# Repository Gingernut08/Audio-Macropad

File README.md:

Full Design:

Schematic:

PCB:

Case:

The Case fits together with 4x M3 Bolts and heatset inserts

BOM
16x Cherry MX Switches
16x DSA Keycaps
4x M3x5x4 Heatset inserts
4x M3x16mm SHCS Bolts
16x 1N4148 DO-35 Diodes.
16x SK6812 MINI-E LEDs
1x 0.91" 128x32 OLED Display
1x XIAO RP2040
1x Case (2 printed parts)

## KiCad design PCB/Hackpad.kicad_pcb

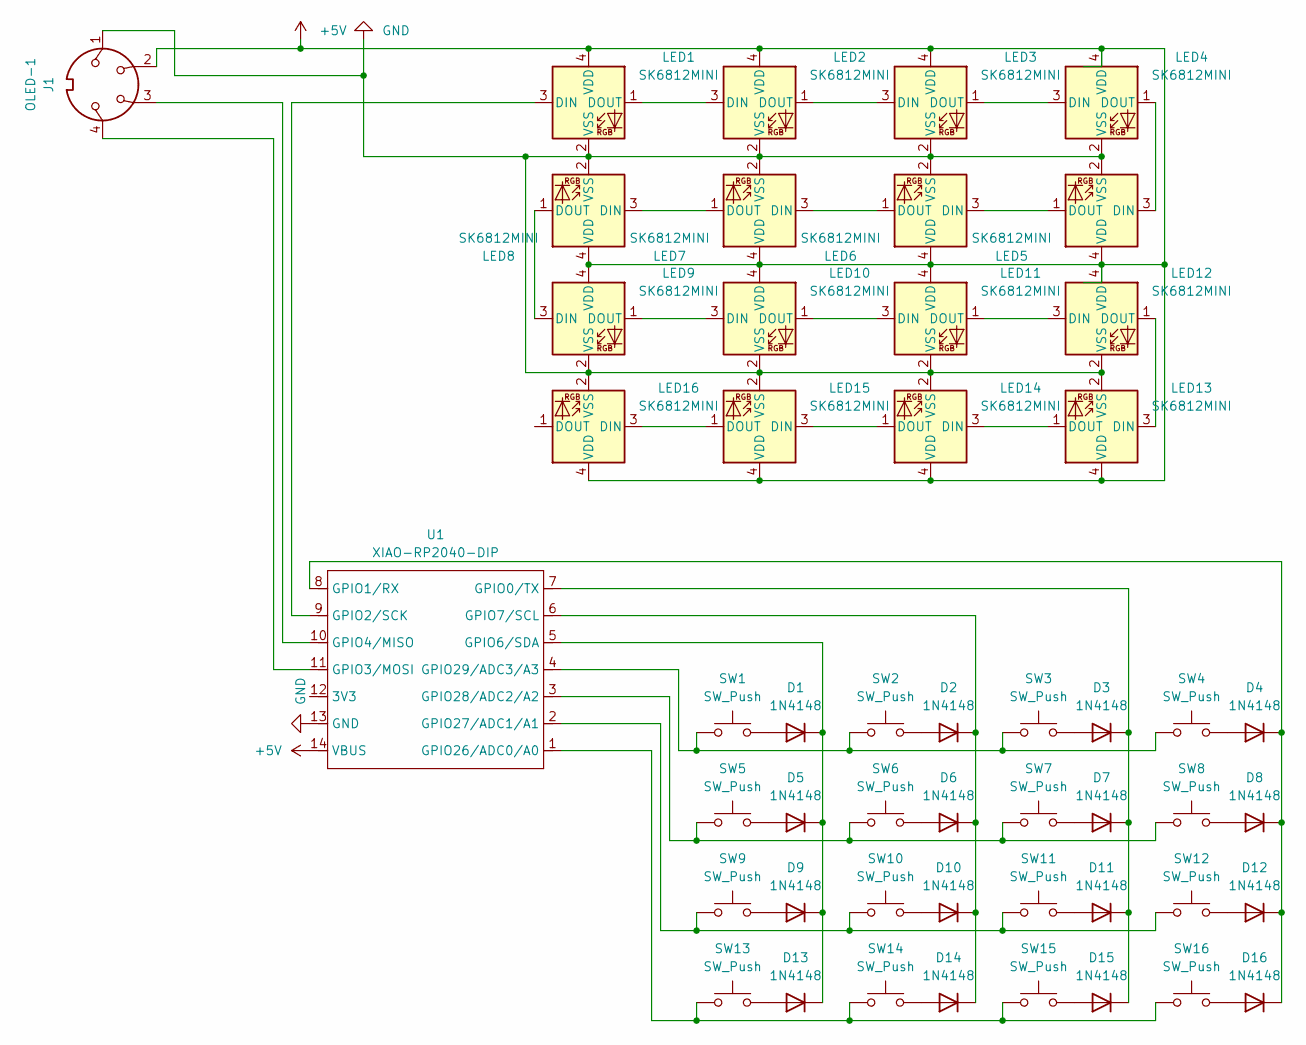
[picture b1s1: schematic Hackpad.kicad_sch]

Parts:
D1, D2, D3, D4, D5, D6, D7, D8, D9, D10, D11, D12, D13, D14, D15, D16: 1N4148; D_DO-35_SOD27_P7.62mm_Horizontal
J1: OLED-1; SSD1306-0.91-OLED-4pin-128x32
LED1, LED2, LED3, LED4, LED5, LED6, LED7, LED8, LED9, LED10, LED11, LED12, LED13, LED14, LED15, LED16: SK6812MINI; LED_SK6812MINI_PLCC4_3.5x3.5mm_P1.75mm
SW1, SW2, SW3, SW4, SW5, SW6, SW7, SW8, SW9, SW10, SW11, SW12, SW13, SW14, SW15, SW16: SW_Push; SW_Cherry_MX_1.00u_PCB
U1: XIAO-RP2040-DIP

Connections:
+5V: J1.2, LED1.4 (VDD), LED2.4 (VDD), LED3.4 (VDD), LED4.4 (VDD), LED5.4 (VDD), LED6.4 (VDD), LED7.4 (VDD), LED8.4 (VDD), LED9.4 (VDD), LED10.4 (VDD), LED11.4 (VDD), LED12.4 (VDD), LED13.4 (VDD), LED14.4 (VDD), LED15.4 (VDD), LED16.4 (VDD), U1.14 (VBUS)
GND: J1.1, LED1.2 (VSS), LED2.2 (VSS), LED3.2 (VSS), LED4.2 (VSS), LED5.2 (VSS), LED6.2 (VSS), LED7.2 (VSS), LED8.2 (VSS), LED9.2 (VSS), LED10.2 (VSS), LED11.2 (VSS), LED12.2 (VSS), LED13.2 (VSS), LED14.2 (VSS), LED15.2 (VSS), LED16.2 (VSS), U1.13 (GND)
unnamed: D1.2 (A), SW1.2
unnamed: D1.1 (K), D5.1 (K), D9.1 (K), D13.1 (K), U1.5 (GPIO6/SDA)
unnamed: D2.2 (A), SW2.2
unnamed: D3.2 (A), SW3.2
unnamed: D4.2 (A), SW4.2
unnamed: D5.2 (A), SW5.2
unnamed: D6.2 (A), SW6.2
unnamed: D7.2 (A), SW7.2
unnamed: D8.2 (A), SW8.2
unnamed: D9.2 (A), SW9.2
unnamed: D10.2 (A), SW10.2
unnamed: D2.1 (K), D6.1 (K), D10.1 (K), D14.1 (K), U1.6 (GPIO7/SCL)
unnamed: D11.2 (A), SW11.2
unnamed: D3.1 (K), D7.1 (K), D11.1 (K), D15.1 (K), U1.7 (GPIO0/TX)
unnamed: D12.2 (A), SW12.2
unnamed: D4.1 (K), D8.1 (K), D12.1 (K), D16.1 (K), U1.8 (GPIO1/RX)
unnamed: D13.2 (A), SW13.2
unnamed: D14.2 (A), SW14.2
unnamed: D15.2 (A), SW15.2
unnamed: D16.2 (A), SW16.2
unnamed: LED1.3 (DIN), U1.9 (GPIO2/SCK)
unnamed: LED1.1 (DOUT), LED2.3 (DIN)
unnamed: LED2.1 (DOUT), LED3.3 (DIN)
unnamed: LED3.1 (DOUT), LED4.3 (DIN)
unnamed: LED4.1 (DOUT), LED5.3 (DIN)
unnamed: LED5.1 (DOUT), LED6.3 (DIN)
unnamed: LED6.1 (DOUT), LED7.3 (DIN)
unnamed: LED7.1 (DOUT), LED8.3 (DIN)
unnamed: LED8.1 (DOUT), LED9.3 (DIN)
unnamed: LED9.1 (DOUT), LED10.3 (DIN)
unnamed: LED10.1 (DOUT), LED11.3 (DIN)
unnamed: LED11.1 (DOUT), LED12.3 (DIN)
unnamed: LED12.1 (DOUT), LED13.3 (DIN)
unnamed: LED13.1 (DOUT), LED14.3 (DIN)
unnamed: LED14.1 (DOUT), LED15.3 (DIN)
unnamed: LED15.1 (DOUT), LED16.3 (DIN)
unnamed: J1.4, U1.11 (GPIO3/MOSI)
unnamed: J1.3, U1.10 (GPIO4/MISO)
unnamed: SW13.1, SW14.1, SW15.1, SW16.1, U1.1 (GPIO26/ADC0/A0)
unnamed: SW9.1, SW10.1, SW11.1, SW12.1, U1.2 (GPIO27/ADC1/A1)
unnamed: SW5.1, SW6.1, SW7.1, SW8.1, U1.3 (GPIO28/ADC2/A2)
unnamed: SW1.1, SW2.1, SW3.1, SW4.1, U1.4 (GPIO29/ADC3/A3)

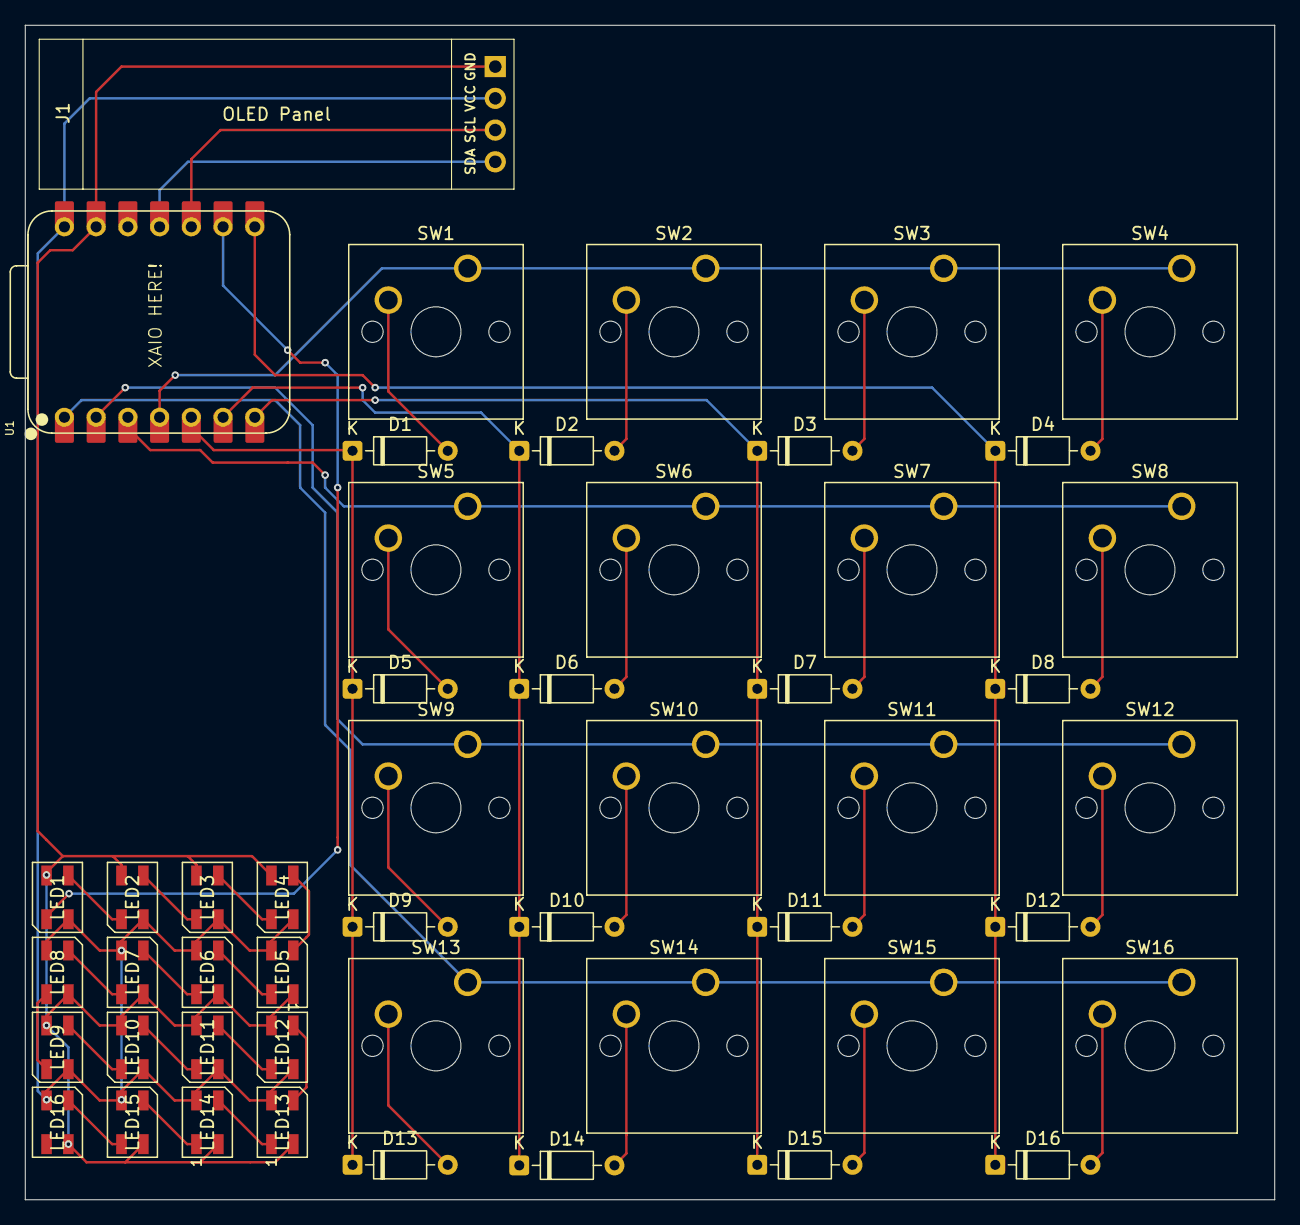
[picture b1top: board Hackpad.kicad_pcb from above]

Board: 2 copper layers, 100.0 x 94.0 mm, 50 parts (0 on the bottom side), 44 nets.

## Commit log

2025-12-12 Added Macropad Case
2025-12-12 Create CAD
2025-12-12 Create temp
2025-12-12 Update README with design and schematic images
    Added images for full design, schematic, PCB, and case.
